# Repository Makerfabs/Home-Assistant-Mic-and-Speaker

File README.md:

# Makerfabs Home Assistant Mic and Speaker

## Intruduce
[Product Link]()

[Wiki Link]()

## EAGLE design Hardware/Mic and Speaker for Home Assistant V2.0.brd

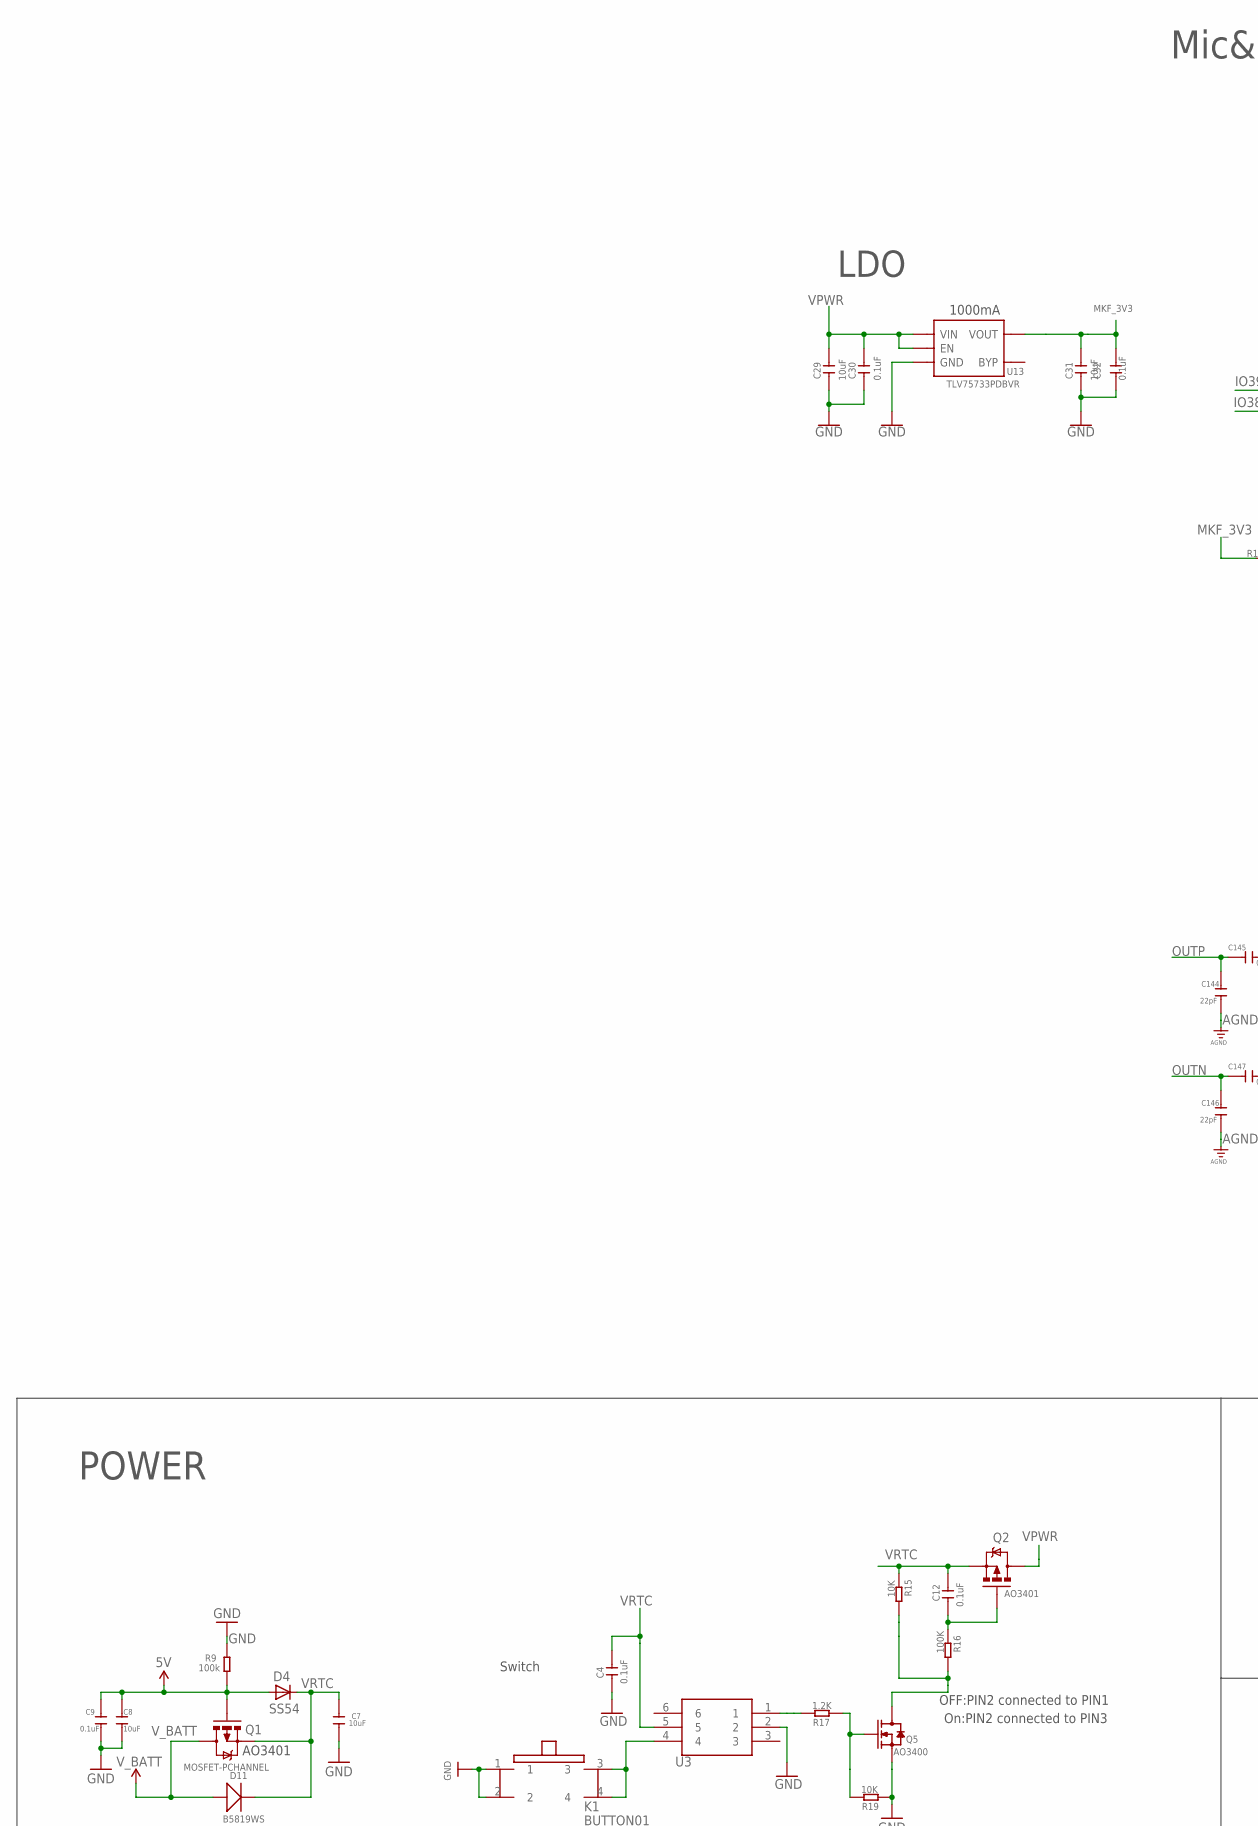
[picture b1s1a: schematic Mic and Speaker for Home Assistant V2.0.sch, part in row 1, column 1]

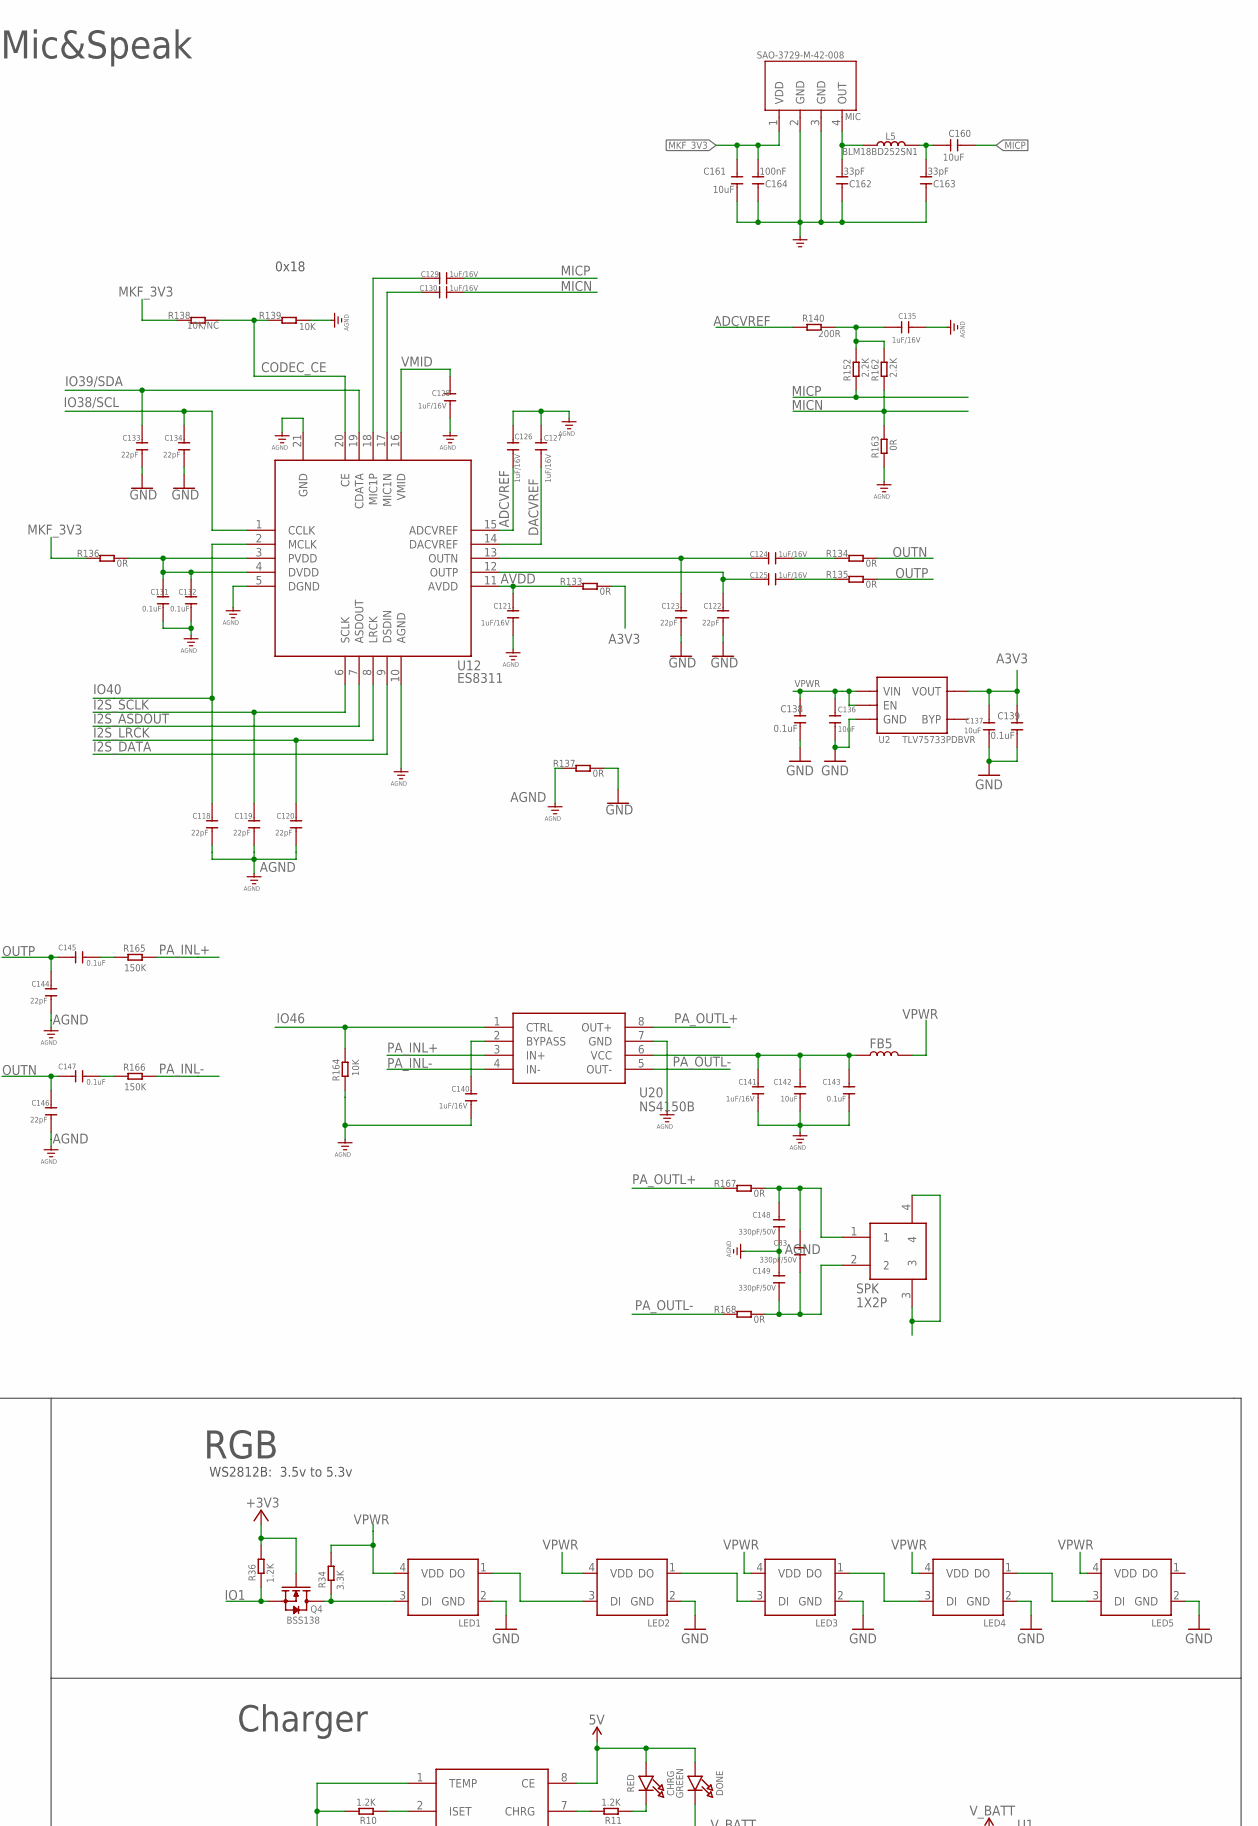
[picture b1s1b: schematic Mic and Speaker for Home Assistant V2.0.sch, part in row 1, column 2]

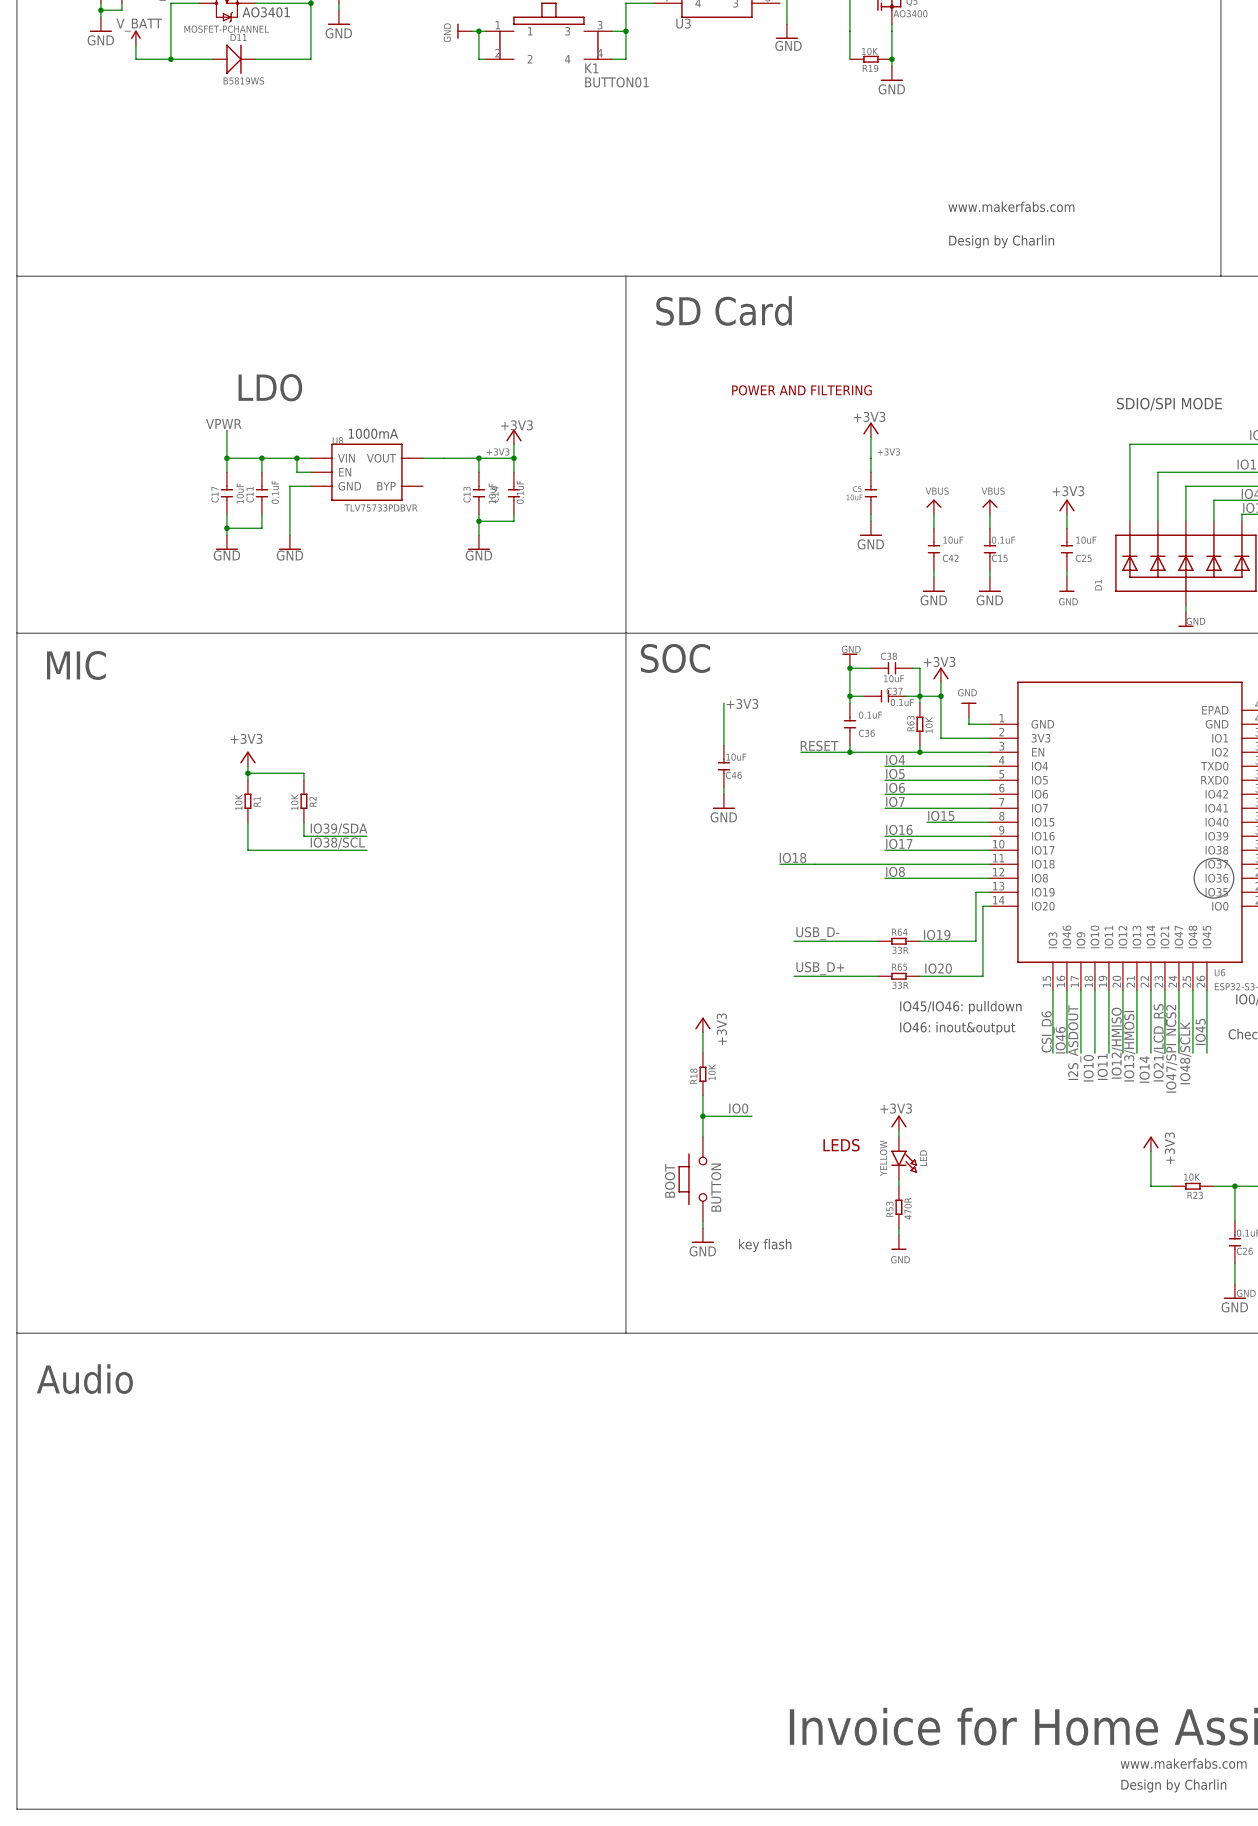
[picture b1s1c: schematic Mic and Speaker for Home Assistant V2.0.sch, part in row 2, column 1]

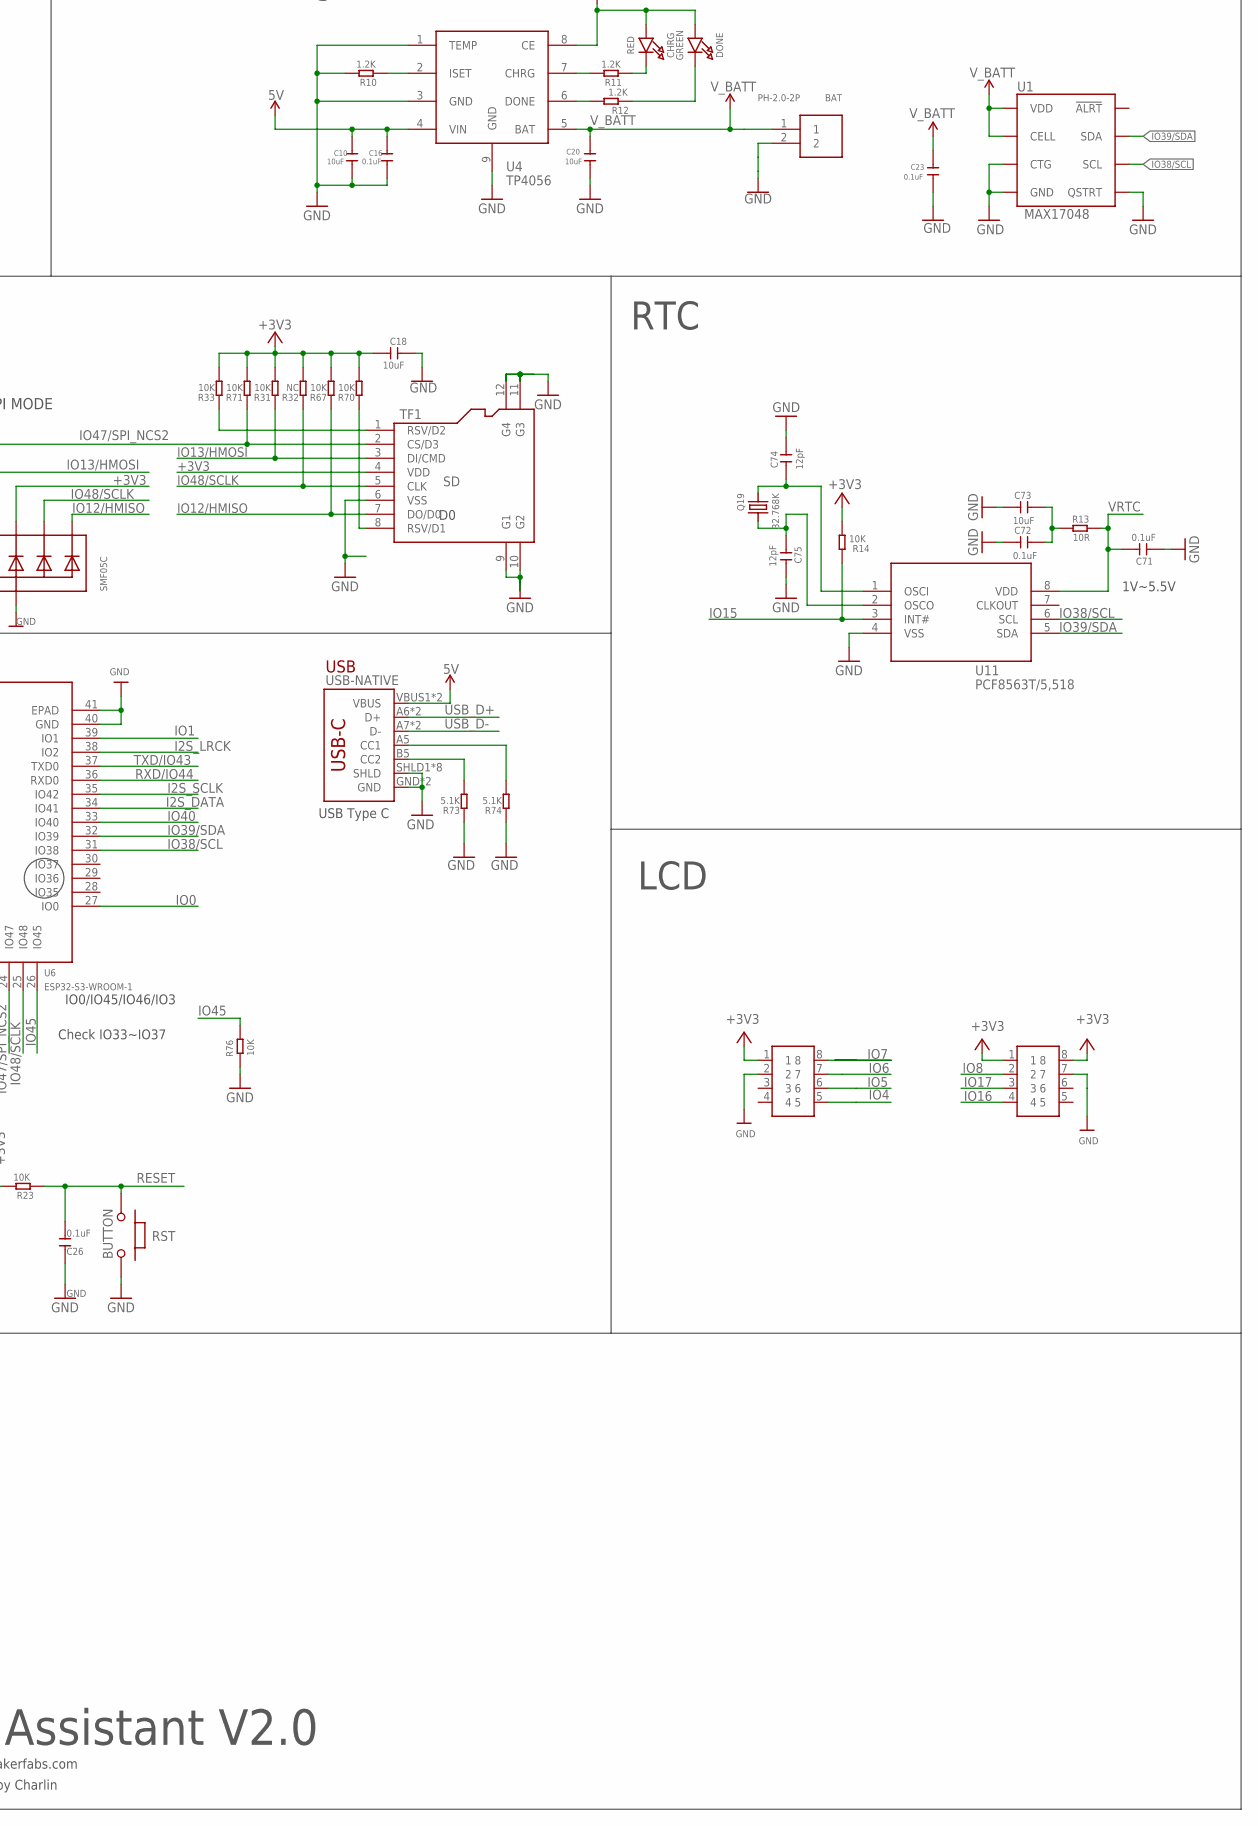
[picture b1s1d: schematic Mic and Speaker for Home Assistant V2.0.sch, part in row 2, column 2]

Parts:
BAT: PH-2.0-2P
BOOT: BUTTON; 157SW
C4, C11, C12, C14, C15, C26, C30, C32, C36, C37, C71, C72: 0.1uF; DISCRETE_C0603
C5, C7, C8, C10, C20, C136, C137, C142, C160, C161: 10uF; C0603
C9, C16, C23, C131, C132, C138, C139, C143, C145, C147: 0.1uF; C0603
C13, C17, C18, C25, C29, C31, C38, C42, C46, C73: 10uF; DISCRETE_C0603
C33, C148, C149: 330pF/50V; C0603
C74, C75: 12pF; DISCRETE_C0603
C118, C119, C120, C122, C123, C133, C134, C144, C146: 22pF; C0603
C121, C124, C125, C126, C127, C128, C129, C130, C135, C140, C141: 1uF/16V; C0603
C162, C163: 33pF; C0603
C164: 100nF; C0603
CHRG: RED; CHIPLED_0805_NOOUTLINE
D1: SMF05C; SOT363
D4: SS54; DO-214AC
D11: B5819WS; SOD323
DONE: GREEN; CHIPLED_0805_NOOUTLINE
FB5: INDUCTORFB-30OHM; 0603
J1, J2: CON2X4-254P-B; CON2X4-2.54MM-THD
K1: BUTTON01
L5: BLM18BD252SN1; L0603
LED: YELLOW; CHIPLED_0805_NOOUTLINE
LED1, LED2, LED3, LED4, LED5: WS2812B-2020
MIC: SAO-3729-M-42-008; MIC4-SMD-3.76X2.95MM
Q1: MOSFET-PCHANNEL; SOT23-3
Q2: AO3401; SOT23-3
Q4: BSS138; SOT23@1
Q5: AO3400; SOT23@1
Q19: 32.768K; XTAL3215
R1, R2, R14, R15, R18, R19, R23, R63, R76, R139, R164: 10K; R0603
R9: 100k; R0603
R10, R11, R12, R17, R36: 1.2K; R0603
R13: 10R; R0603
R16: 100K; R0603
R31, R33, R67, R70, R71: 10K; DISCRETE_R0603
R32: NC; DISCRETE_R0603
R34: 3.3K; R0603
R53: 470R; R0603
R64, R65: 33R; R0603
R73, R74: 5.1K; DISCRETE_R0603
R133, R134, R135, R136, R137, R163, R167, R168: 0R; R0603
R138: 10K/NC; R0603
R140: 200R; R0603
R152, R162: 2.2K; R0603
R165, R166: 150K; R0603
RST: BUTTON; 157SW
SPK: 1X2P; 1X2P-SMT1.25MM
TF1: SD; 8P-SMD
U1: MAX17048; DFN-8
U2, U8, U13: TLV75733PDBVR; SOT23-5
U3: SW01A; SOT23-6-95P-300L300W
U4: TP4056; SOP8-1.27P
U6: ESP32-S3-WROOM-1
U11: PCF8563T/5,518; SOP8
U12: ES8311; QFN20-40P-300L300W55H
U20: NS4150B; MSOP8-65P-490L300W110H
USB-NATIVE: USB_C5; USB-C-16P-5

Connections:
5V: C8.2, C9.1, C10.1, C16.1, CHRG.A, D4.A, DONE.A, Q1.1 (G), R9.1, U4.4 (VIN), U4.8 (CE), USB-NATIVE.VBUS1 (VBUS), USB-NATIVE.VBUS2 (VBUS)
+3V3: C5.1, C13.2, C14.2, C18.2, C25.2, C37.1, C38.1, C46.2, D1.4 (C3), J1.1, J2.1, J2.8, LED.A, Q4.1 (G), R1.1, R2.1, R14.1, R18.2, R23.2, R31.2, R32.2, R33.2, R36.2, R63.2, R67.2, R70.2, R71.2, TF1.4 (VDD), U6.2 (3V3), U8.5 (VOUT)
A3V3: C137.1, C139.2, R133.2, U2.5 (VOUT)
ADCVREF: C126.2, R140.1, U12.15 (ADCVREF)
AGND: C118.2, C119.2, C120.2, C121.2, C126.1, C127.1, C128.2, C131.2, C132.2, C135.2, C140.2, C141.2, C142.2, C143.2, C144.2, C146.2, C148.2, C149.1, C161.1, C162.2, C163.2, C164.2, MIC.2 (GND), MIC.3 (GND), R137.1, R139.2, R163.1, R164.1, U12.5 (DGND), U12.10 (AGND), U12.21 (GND), U20.7 (GND)
AVDD: C121.1, R133.1, U12.11 (AVDD)
CODEC_CE: R138.2, R139.1, U12.20 (CE)
CSI_D6: U6.15 (IO3)
DACVREF: C127.2, U12.14 (DACVREF)
GND: BAT.2, BOOT.1, C4.1, C5.2, C7.1, C8.1, C9.2, C10.2, C11.1, C13.1, C14.1, C15.1, C16.2, C17.1, C18.1, C20.2, C23.2, C25.1, C26.1, C29.1, C30.1, C31.1, C32.1, C36.2, C37.2, C38.2, C42.1, C46.1, C71.1, C72.1, C73.1, C74.2, C75.2, C122.2, C123.2, C133.2, C134.2, C136.2, C137.2, C138.1, C139.1, D1.2 (A), J1.2, J2.7, K1.1, K1.2, LED1.2 (GND), LED2.2 (GND), LED3.2 (GND), LED4.2 (GND), LED5.2 (GND), Q5.2 (S), R9.2, R10.2, R19.1, R53.1, R73.1, R74.1, R76.1, R137.2, RST.1, SPK.3, SPK.4, TF1.6 (VSS), TF1.9 (G1), TF1.10 (G2), TF1.11 (G3), TF1.12 (G4), U1.1 (CTG), U1.4 (GND), U1.6 (QSTRT), U1.9 (GND), U2.2 (GND), U3.2, U4.1 (TEMP), U4.3 (GND), U4.9 (GND), U6.1 (GND), U6.40 (GND), U6.41 (EPAD), U8.2 (GND), U11.4 (VSS), U13.2 (GND), USB-NATIVE.GND, USB-NATIVE.GND2 (GND), USB-NATIVE.SHLD1 (SHLD), USB-NATIVE.SHLD2 (SHLD), USB-NATIVE.SHLD3 (SHLD), USB-NATIVE.SHLD4 (SHLD), USB-NATIVE.SHLD5 (SHLD), USB-NATIVE.SHLD6 (SHLD), USB-NATIVE.SHLD7 (SHLD), USB-NATIVE.SHLD8 (SHLD)
I2S_ASDOUT: U6.17 (IO9), U12.7 (ASDOUT)
I2S_DATA: U6.34 (IO41), U12.9 (DSDIN)
I2S_LRCK: C120.1, U6.38 (IO2), U12.8 (LRCK)
I2S_SCLK: C119.1, U6.35 (IO42), U12.6 (SCLK)
IO0: BOOT.2, R18.1, U6.27 (IO0)
IO1: Q4.2 (S), R36.1, U6.39 (IO1)
IO4: J1.5, U6.4 (IO4)
IO5: J1.6, U6.5 (IO5)
IO6: J1.7, U6.6 (IO6)
IO7: J1.8, U6.7 (IO7)
IO8: J2.2, U6.12 (IO8)
IO10: U6.18 (IO10)
IO11: U6.19 (IO11)
IO12/HMISO: D1.6 (C5), R67.1, TF1.7 (DO/D0), U6.20 (IO12)
IO13/HMOSI: D1.3 (C2), R31.1, TF1.3 (DI/CMD), U6.21 (IO13)
IO14: U6.22 (IO14)
IO15: R14.2, U6.8 (IO15), U11.3 (INT#)
IO16: J2.4, U6.9 (IO16)
IO17: J2.3, U6.10 (IO17)
IO18: U6.11 (IO18)
IO19: R64.2, U6.13 (IO19)
IO20: R65.2, U6.14 (IO20)
IO21/LCD_RS: U6.23 (IO21)
IO38/SCL: C134.1, R1.2, U1.7 (SCL), U6.31 (IO38), U11.6 (SCL), U12.1 (CCLK)
IO39/SDA: C133.1, R2.2, U1.8 (SDA), U6.32 (IO39), U11.5 (SDA), U12.19 (CDATA)
IO40: C118.1, U6.33 (IO40), U12.2 (MCLK)
IO45: R76.2, U6.26 (IO45)
IO46: R164.2, U6.16 (IO46), U20.1 (CTRL)
IO47/SPI_NCS2: D1.1 (C1), R71.1, TF1.2 (CS/D3), U6.24 (IO47)
IO48/SCLK: D1.5 (C4), R32.1, TF1.5 (CLK), U6.25 (IO48)
MICN: C130.2, R162.1, R163.2
MICP: C129.2, C160.2, R152.1
MKF_3V3: C31.2, C32.2, C161.2, C164.1, MIC.1 (VDD), R136.1, R138.1, U13.5 (VOUT)
unnamed: R10.1, U4.2 (ISET)
unnamed: R11.2, U4.7 (CHRG)
unnamed: R12.2, U4.6 (DONE)
unnamed: C12.1, Q2.1 (G), R16.1
unnamed: CHRG.C, R11.1
unnamed: DONE.C, R12.1
unnamed: Q5.3 (D), R15.2, R16.2
unnamed: LED.C, R53.2
unnamed: LED1.3 (DI), Q4.3 (D), R34.1
unnamed: R33.1, TF1.1 (RSV/D2)
unnamed: R70.1, TF1.8 (RSV/D1)
unnamed: K1.3, K1.4, U3.4
unnamed: Q5.1 (G), R17.1, R19.2
unnamed: R17.2, U3.1
unnamed: C145.2, R165.1
unnamed: LED1.1 (DO), LED2.3 (DI)
unnamed: LED2.1 (DO), LED3.3 (DI)
unnamed: C147.2, R166.1
unnamed: C33.2, C149.2, R168.2, SPK.2
unnamed: LED3.1 (DO), LED4.3 (DI)
unnamed: LED4.1 (DO), LED5.3 (DI)
unnamed: R74.2, USB-NATIVE.A5 (CC1)
unnamed: R73.2, USB-NATIVE.B5 (CC2)
unnamed: C160.1, C163.1, L5.2
unnamed: C130.1, U12.17 (MIC1N)
unnamed: C162.1, L5.1, MIC.4 (OUT)
unnamed: C122.1, C125.1, U12.12 (OUTP)
unnamed: C123.1, C124.1, U12.13 (OUTN)
unnamed: C124.2, R134.1
unnamed: C125.2, R135.1
unnamed: C129.1, U12.18 (MIC1P)
unnamed: C131.1, C132.1, R136.2, U12.3 (PVDD), U12.4 (DVDD)
unnamed: C135.1, R140.2, R152.2, R162.2
unnamed: C140.1, U20.2 (BYPASS)
unnamed: C141.1, C142.1, C143.1, FB5.1, U20.6 (VCC)
unnamed: C74.1, Q19.P$1 (1), U11.1 (OSCI)
unnamed: C75.1, Q19.P$2 (2), U11.2 (OSCO)
unnamed: C72.2, C73.2, R13.1
unnamed: C33.1, C148.1, R167.2, SPK.1
OUTN: C146.1, C147.1, R134.2
OUTP: C144.1, C145.1, R135.2
PA_INL+: R165.2, U20.3 (IN+)
PA_INL-: R166.2, U20.4 (IN-)
PA_OUTL+: R167.1, U20.8 (OUT+)
PA_OUTL-: R168.1, U20.5 (OUT-)
RESET: C26.2, C36.1, R23.1, R63.1, RST.2, U6.3 (EN)
RXD/IO44: U6.36 (RXD0)
TXD/IO43: U6.37 (TXD0)
USB_D+: R65.1, USB-NATIVE.A6 (D+), USB-NATIVE.B6 (D+)
USB_D-: R64.1, USB-NATIVE.A7 (D-), USB-NATIVE.B7 (D-)
VMID: C128.1, U12.16 (VMID)
VPWR: C11.2, C15.2, C17.2, C29.2, C30.2, C42.2, C136.1, C138.2, FB5.2, LED1.4 (VDD), LED2.4 (VDD), LED3.4 (VDD), LED4.4 (VDD), LED5.4 (VDD), Q2.3 (D), R34.2, U2.1 (VIN), U2.3 (EN), U8.1 (VIN), U8.3 (EN), U13.1 (VIN), U13.3 (EN)
VRTC: C4.2, C7.2, C12.2, C71.2, D4.C, D11.-, Q1.2 (S), Q2.2 (S), R13.2, R15.1, U3.5, U11.8 (VDD)
V_BATT: BAT.1, C20.1, C23.1, D11.+, Q1.3 (D), U1.2 (CELL), U1.3 (VDD), U4.5 (BAT)

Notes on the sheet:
www.makerfabs.com
Design by Charlin
LEDS
POWER AND FILTERING
key flash
Invoice for Home Assistant V2.0
POWER
SD Card
IO45/IO46: pulldown
IO46: inout&output
USB
USB Type C
IO0/IO45/IO46/IO3
Check IO33~IO37
SOC
SDIO/SPI MODE
Charger
AO3401
1V~5.5V
WS2812B: 3.5v to 5.3v
RGB
Switch
On:PIN2 connected to PIN3
OFF:PIN2 connected to PIN1
1000mA
LDO
LCD
RTC
MIC
Audio
Mic&Speak
0x18

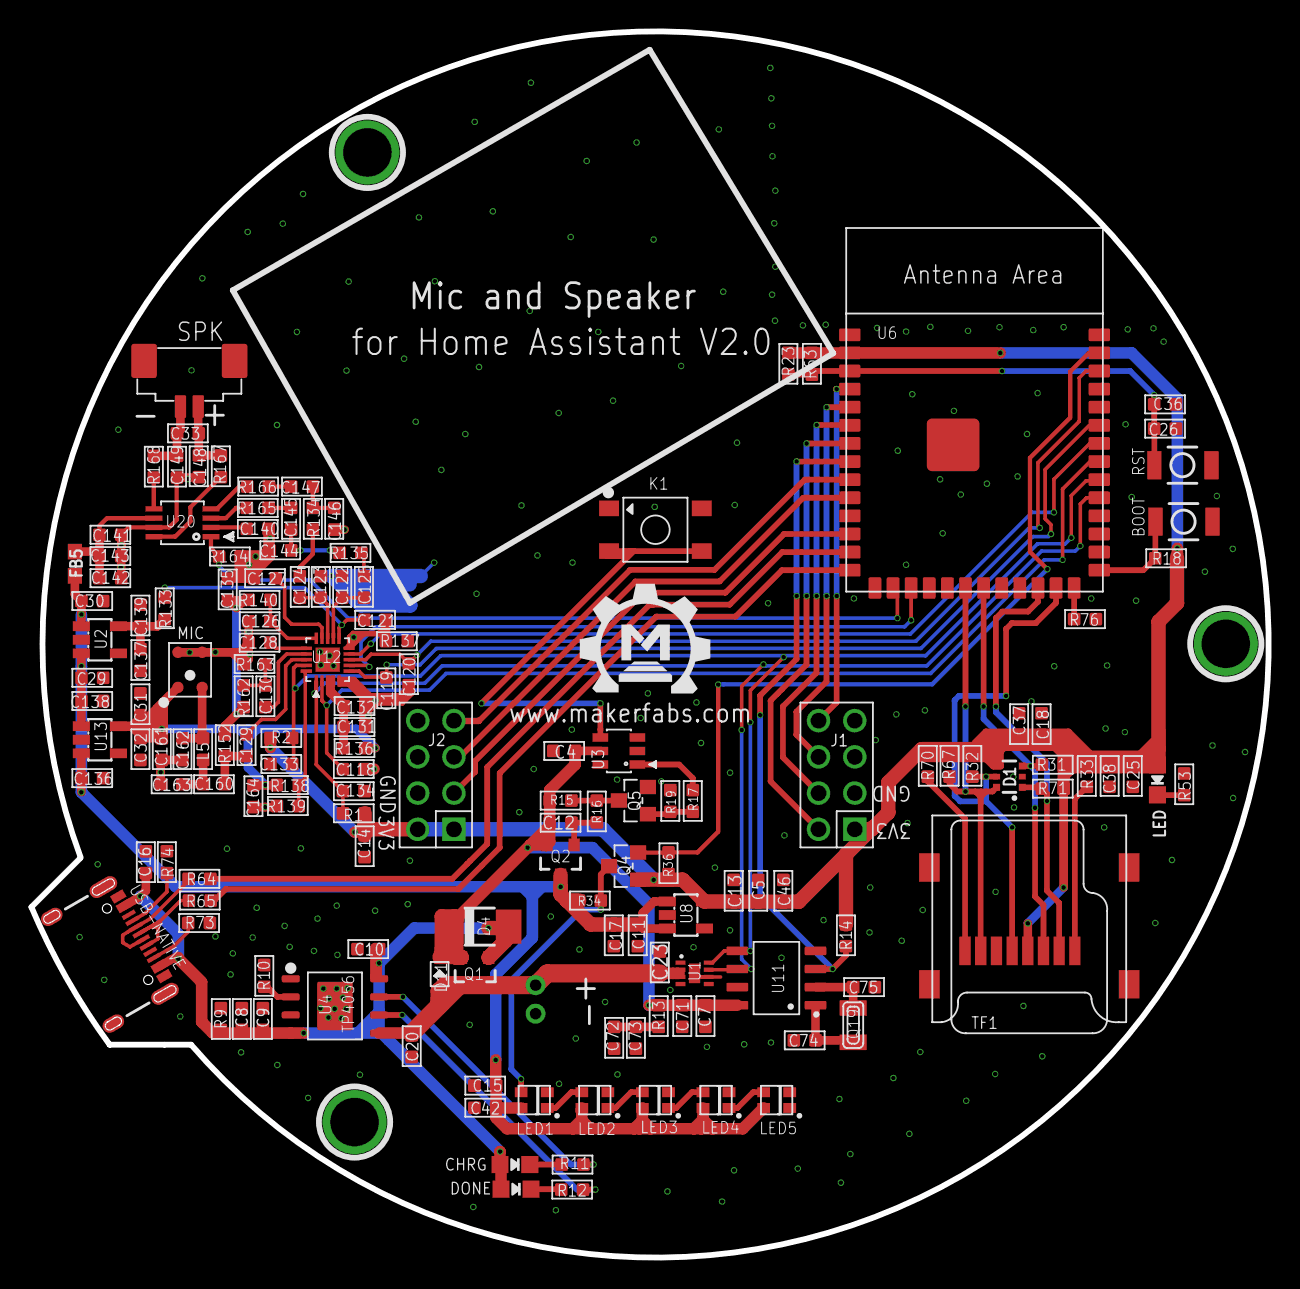
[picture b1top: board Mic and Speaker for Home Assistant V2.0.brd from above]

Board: 2 copper layers, 86.8 x 86.0 mm, 154 parts (1 on the bottom side), 89 nets.

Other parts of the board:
U$1: MAKERFABS_0.3

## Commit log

2026-04-21 Create Project
2026-05-20 fix yaml
2026-05-20 Add hardware

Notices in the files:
parts and their libraries:
microbuilder: This work is placed in the public domain, and may be freely used for commercial and non-commercial work with the following conditions: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
SparkFun-IC-Power: Licensing: Creative Commons ShareAlike 4.0 International - https://creativecommons.org/licenses/by-sa/4.0
